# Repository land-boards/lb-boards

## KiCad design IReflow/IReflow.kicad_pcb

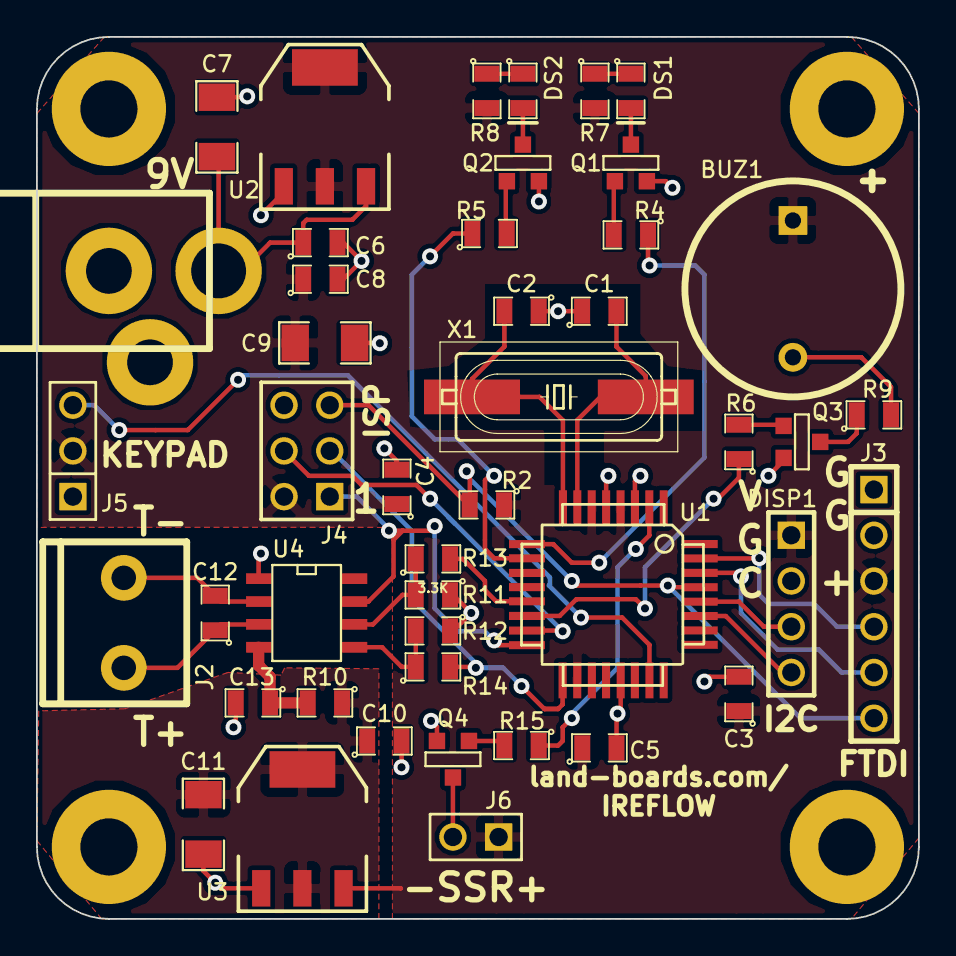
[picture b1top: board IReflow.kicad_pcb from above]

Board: 2 copper layers, 49.0 x 49.0 mm, 49 parts (0 on the bottom side), 36 nets.

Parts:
BUZ1: BUZZER; PIEZO_12MM
C1, C2: 18pF; SM0805
C3, C4, C5, C6, C8, C10, C13: 0.1uF; SM0805
C7, C9, C11: 10uF; SM1206
C12: 0.01uF; SM0805
DISP1: I2C_OLED_128X64; PIN_ARRAY_4X1
DS1, DS2: LED; SM0805
J1: DCJ0202; JACK_2.1MM
J2: CONN_2; TB2-5MM
J3: FTDI; PIN_ARRAY_6X1
J4: ISP; PIN_ARRAY_3X2
J5: GVS; PIN_ARRAY_3X1
J6: CONN_2; PIN_ARRAY_2X1
MTG1, MTG2, MTG3, MTG4: CONN_1; MTG-4-40
Q1, Q2, Q3, Q4: 2N3904; SOT23EBC
R2, R4, R5, R6, R15: 10K; SM0805
R7, R8: 330; SM0805
R9: 100; SM0805
R10: 10; SM0805
R11, R12: 3.3K; SM0805
R13, R14: 2.7K; SM0805
U1: ATMEGA328-AU; TQFP32
U2: AP1117-5.0; SOT223
U3: AP1117; SOT223
U4: MAX31855; SO8E
X1: 16.0MHz; crystal-HC49UP

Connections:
+5V: BUZ1.1, C3.1, C4.1, C5.1, C8.1, C9.1, DISP1.1, J3.3, J4.2, J5.2, J6.1, R2.1, R7.2, R8.2, U1.4, U1.6, U1.18, U2.2, U2.4, U3.3
/CPU/BUZZ: R6.1, U1.14
/CPU/CS: R13.2, U1.13
/CPU/DS1: R4.1, U1.9
/CPU/DS2: R5.1, U1.10
/CPU/MISO: J4.1, U1.16, U4.7
/CPU/MOSI: J4.4, U1.15
/CPU/RESET: J3.6, J4.5, R2.2, U1.29
/CPU/RXD: J3.5, U1.30
/CPU/SCK: J4.3, R14.2, U1.17
/CPU/SCL: DISP1.3, U1.28
/CPU/SDA: DISP1.4, U1.27
/CPU/SSR: R15.1, U1.2
/CPU/SW5WAY: J5.3, U1.23
/CPU/TXD: J3.4, U1.31
/CPU/XTAL1: C1.2, U1.7, X1.2
/CPU/XTAL2: C2.2, U1.8, X1.1
/Power Supply/+3.3V: C10.1, C11.1, R10.1, U3.2, U3.4
/Thermocoupler Amplifier/THERMO+: C12.1, J2.1, U4.3
/Thermocoupler Amplifier/THERMO-: C12.2, J2.2, U4.2
/Thermocoupler Amplifier/V33COND: C13.1, R10.2, U4.4
GND: C1.1, C2.1, C3.2, C4.2, C5.2, C6.2, C7.2, C8.2, C9.2, C10.2, C11.2, C13.2, DISP1.2, J1.2, J1.3, J3.1, J3.2, J4.6, J5.1, Q1.1, Q2.1, Q3.1, Q4.1, R11.1, R12.1, U1.3, U1.5, U1.21, U2.1, U3.1, U4.1
unnamed: Q3.3, R9.1
unnamed: J6.2, Q4.3
unnamed: Q4.2, R15.2
unnamed: Q1.2, R4.2
unnamed: DS1.1, R7.1
unnamed: DS1.2, Q1.3
unnamed: Q3.2, R6.2
unnamed: BUZ1.2, R9.2
unnamed: DS2.1, R8.1
unnamed: DS2.2, Q2.3
unnamed: Q2.2, R5.2
unnamed: R11.2, R13.1, U4.6
unnamed: R12.2, R14.1, U4.5
unnamed: C6.1, C7.1, J1.1, U2.3

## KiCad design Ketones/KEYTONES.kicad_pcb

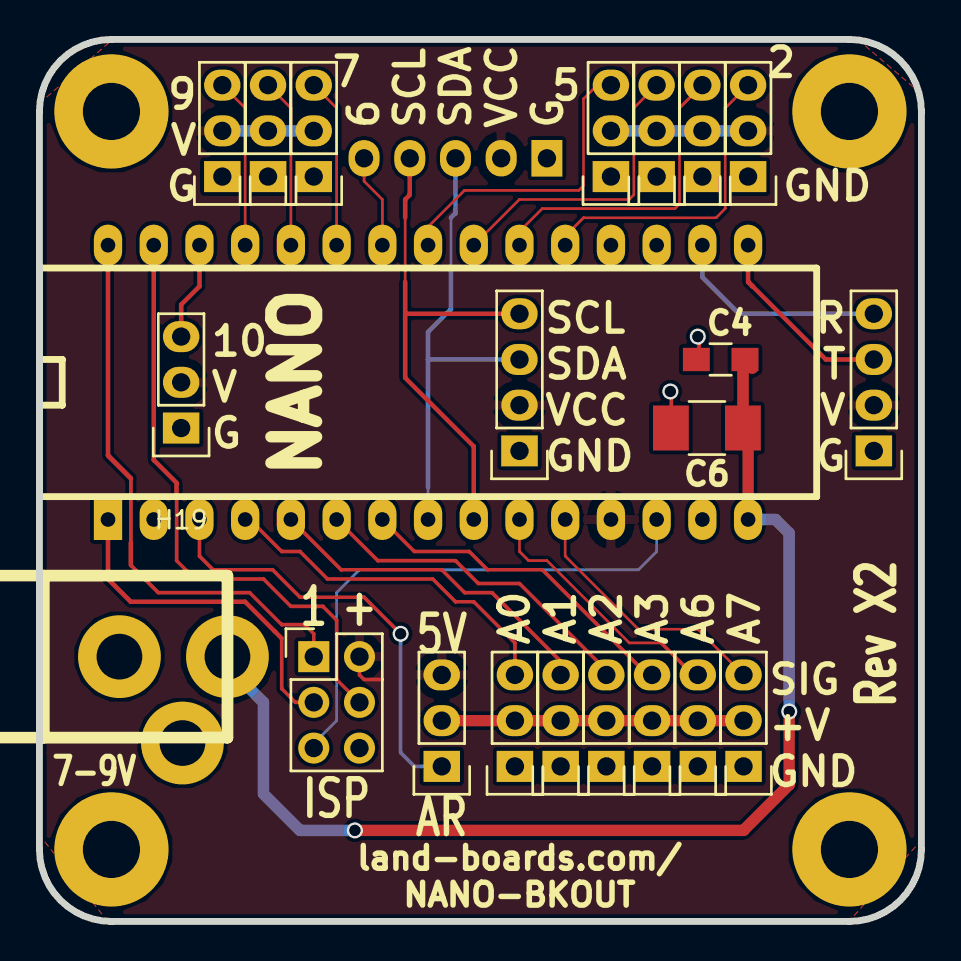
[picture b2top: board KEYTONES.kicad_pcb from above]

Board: 2 copper layers, 49.0 x 49.0 mm, 27 parts (1 on the bottom side), 28 nets.

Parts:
C4: 0.1uF; R_0805_HandSoldering
C6: 22uF; R_1210_HandSoldering
H1, H2, H3, H4, H5, H6, H9, H10, H11, H12, H14, H15, H16, H18, H19: CONN_01X03; Pin_Header_Straight_1x03
H7: CONN_01X05; Pin_Header_Straight_1x05
H8: CONN_02X03; Pin_Header_Straight_2x03
H13, H17: CONN_01X04; Pin_Header_Straight_1x04
J1: DCJ0202; DCJ-NEW
MTG1, MTG2, MTG3, MTG4: CONN_1; MTG-4-40
U5: arduino_nano; arduino_mini

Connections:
+5V: H7.2, H8.2, H9.2, H10.2, H11.2, H12.2, H13.2, H14.2, H15.2, H16.2, H17.2, H18.3, H19.2, U5.12
+9V: C4.1, C6.1, J1.1, U5.15
/A0: H1.3, U5.4
/A1: H2.3, U5.5
/A2: H3.3, U5.6
/A3: H4.3, U5.7
/A6: H5.3, U5.10
/A7: H6.3, U5.11
/AREF: H18.1, U5.3
/D0: H17.3, U5.16
/D1: H17.4, U5.17
/D2: H16.3, U5.20
/D3: H15.3, U5.21
/D4: H14.3, U5.22
/D5: H12.3, U5.23
/D6: H7.5, U5.24
/D7: H11.3, U5.25
/D8: H10.3, U5.26
/D9: H9.3, U5.27
/D10: H19.3, U5.28
/D11: H8.4, U5.29
/D12: H8.1, U5.30
/D13: H8.3, U5.1
/SCL: H7.4, H13.4, U5.9
/SDA: H7.3, H13.3, U5.8
/~RST: H8.5, U5.13
GND: C4.2, C6.2, H1.1, H2.1, H3.1, H4.1, H5.1, H6.1, H7.1, H8.6, H9.1, H10.1, H11.1, H12.1, H13.1, H14.1, H15.1, H16.1, H17.1, H19.1, J1.2, J1.3, U5.14, U5.19
unnamed: H1.2, H2.2, H3.2, H4.2, H5.2, H6.2, H18.2

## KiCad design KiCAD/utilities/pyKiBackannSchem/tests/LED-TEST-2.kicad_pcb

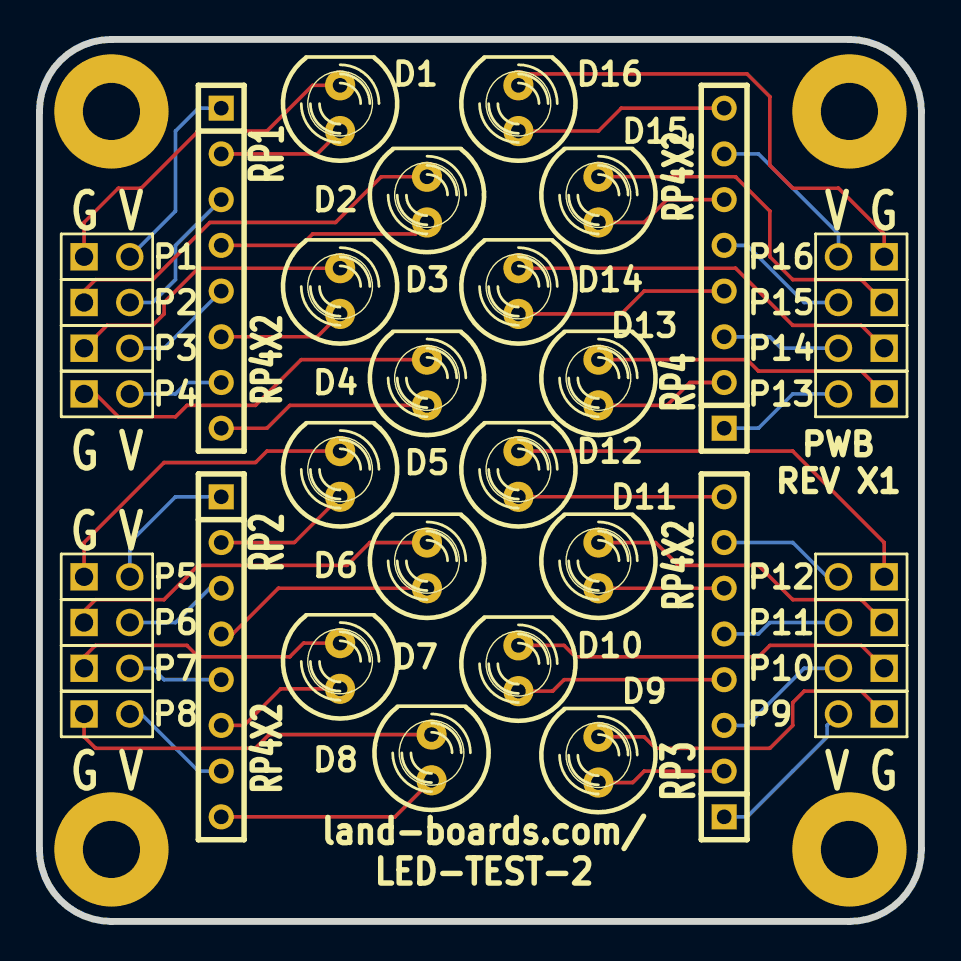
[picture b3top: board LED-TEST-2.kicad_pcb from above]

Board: 2 copper layers, 49.0 x 49.0 mm, 40 parts (0 on the bottom side), 48 nets.

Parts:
D1, D2, D3, D4, D5, D6, D7, D8, D9, D10, D11, D12, D13, D14, D15, D16: LED; LED-5MM
MTG1, MTG2, MTG3, MTG4: CONN_1; MTG-4-40
P1, P2, P3, P4, P5, P6, P7, P8, P9, P10, P11, P12, P13, P14, P15, P16: CONN_2; PIN_ARRAY_2X1
RP1, RP2, RP3, RP4: RP4X2; SIL-8

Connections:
unnamed: D1.1, RP1.2
unnamed: D1.2, P1.1
unnamed: D2.1, RP1.4
unnamed: D2.2, P2.1
unnamed: D3.1, RP1.6
unnamed: D3.2, P3.1
unnamed: D4.1, RP1.8
unnamed: D4.2, P4.1
unnamed: D5.1, RP2.2
unnamed: D5.2, P5.1
unnamed: D6.1, RP2.4
unnamed: D6.2, P6.1
unnamed: D7.1, RP2.6
unnamed: D7.2, P7.1
unnamed: D8.1, RP2.8
unnamed: D8.2, P8.1
unnamed: D9.1, RP3.2
unnamed: D9.2, P9.1
unnamed: D10.1, RP3.4
unnamed: D10.2, P10.1
unnamed: D11.1, RP3.6
unnamed: D11.2, P11.1
unnamed: D12.1, RP3.8
unnamed: D12.2, P12.1
unnamed: D13.1, RP4.2
unnamed: D13.2, P13.1
unnamed: D14.1, RP4.4
unnamed: D14.2, P14.1
unnamed: D15.1, RP4.6
unnamed: D15.2, P15.1
unnamed: D16.1, RP4.8
unnamed: D16.2, P16.1
unnamed: P1.2, RP1.1
unnamed: P2.2, RP1.3
unnamed: P3.2, RP1.5
unnamed: P4.2, RP1.7
unnamed: P5.2, RP2.1
unnamed: P6.2, RP2.3
unnamed: P7.2, RP2.5
unnamed: P8.2, RP2.7
unnamed: P9.2, RP3.1
unnamed: P10.2, RP3.3
unnamed: P11.2, RP3.5
unnamed: P12.2, RP3.7
unnamed: P13.2, RP4.1
unnamed: P14.2, RP4.3
unnamed: P15.2, RP4.5
unnamed: P16.2, RP4.7

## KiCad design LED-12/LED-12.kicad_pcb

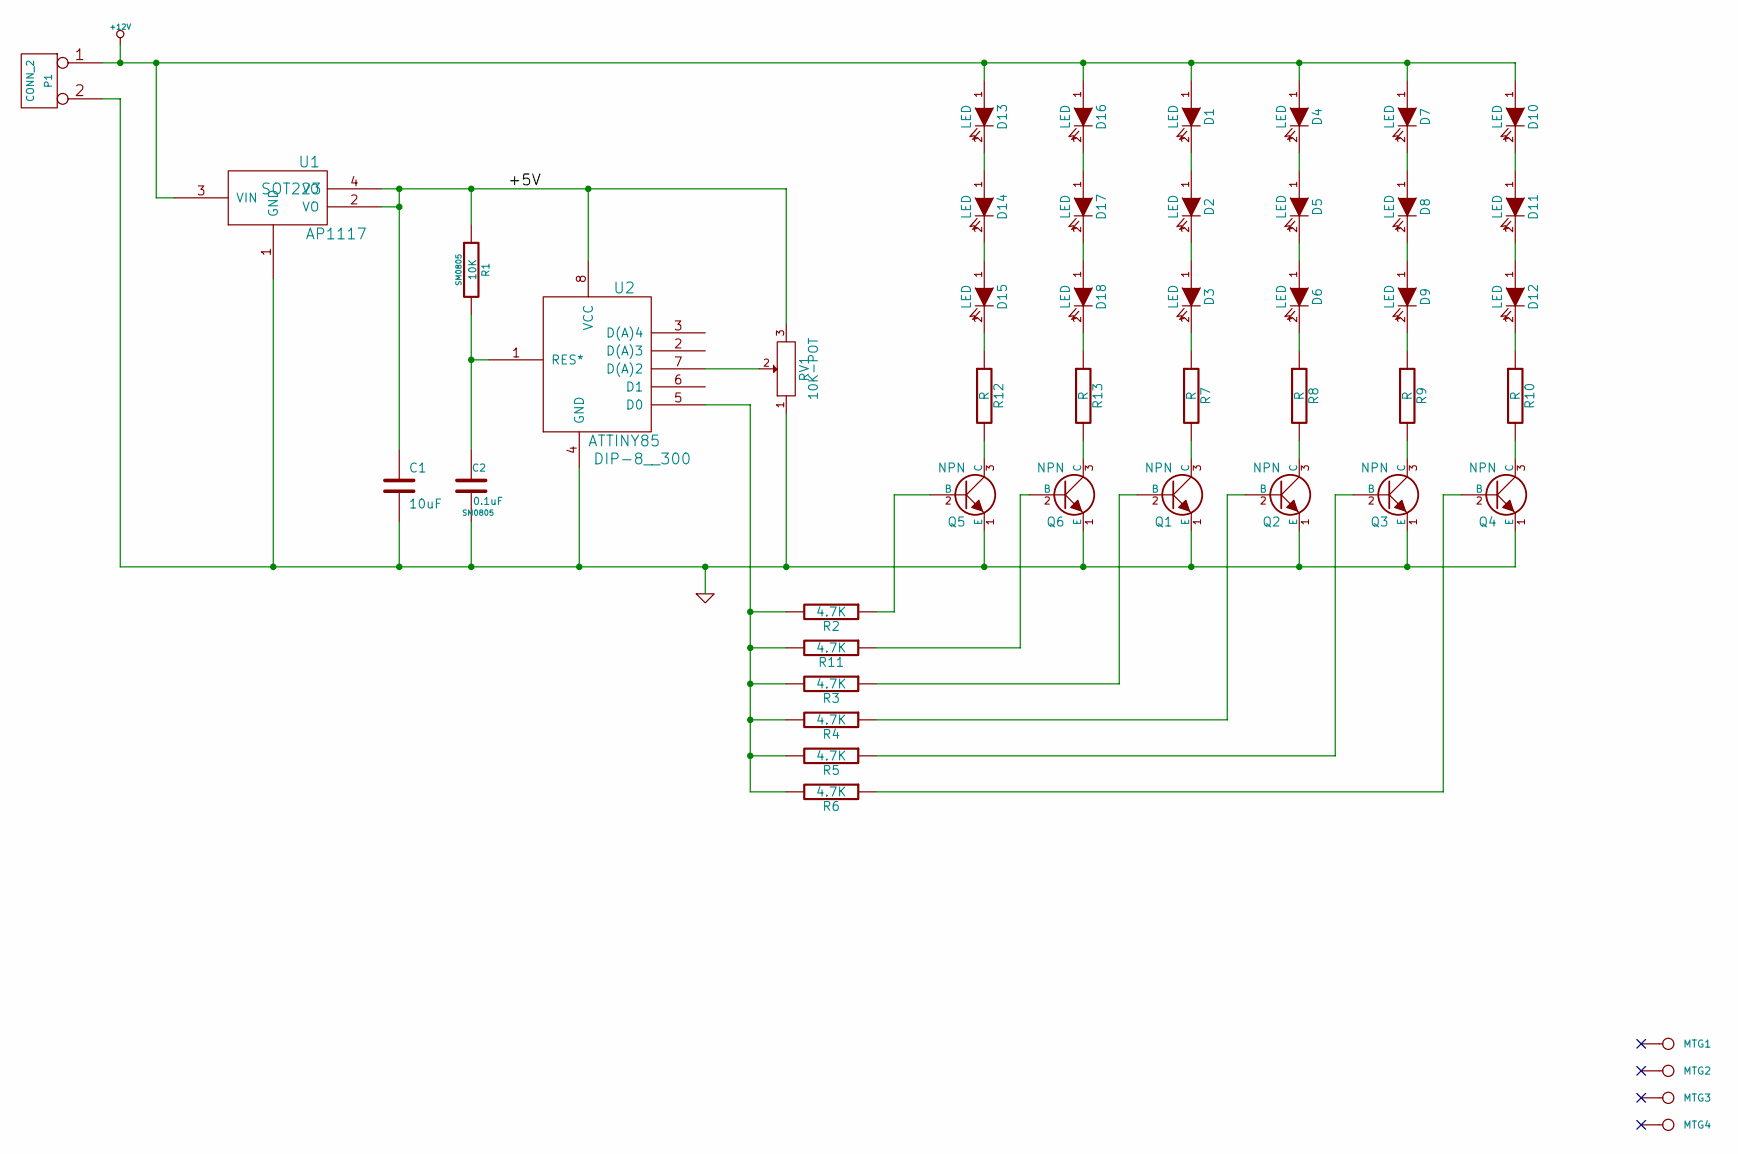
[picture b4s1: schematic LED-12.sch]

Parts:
C1: 10uF; SM1210
C2: 0.1uF; SM0805
D1, D2, D3, D4, D5, D6, D7, D8, D9, D10, D11, D12, D13, D14, D15, D16, D17, D18: LED; LED-5MM
MTG1, MTG2, MTG3, MTG4: CONN_1; MTG-4-40
P1: CONN_2; TB2-5MM
Q1, Q2, Q3, Q4, Q5, Q6: NPN; TO92-123
R1: 10K; SM0805
R2, R3, R4, R5, R6, R11: 4.7K; SM0805
R7, R8, R9, R10, R12, R13: R; SM0805
RV1: 10K-POT; PIN_ARRAY_3X1
U1: AP1117; SOT223
U2: ATTINY85; DIP-8__300

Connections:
+12V: D1.1 (A), D4.1 (A), D7.1 (A), D10.1 (A), D13.1 (A), D16.1 (A), P1.1, U1.3 (VIN)
/+5V: C1.1, R1.1, RV1.3, U1.2 (VO), U1.4 (VO), U2.8 (VCC)
GND: C1.2, C2.2, P1.2 (PM), Q1.1 (E), Q2.1 (E), Q3.1 (E), Q4.1 (E), Q5.1 (E), Q6.1 (E), RV1.1, U1.1 (GND), U2.4 (GND)
unnamed: C2.1, R1.2, U2.1 (RES*)
unnamed: RV1.2, U2.7 (D(A)2)
unnamed: D16.2 (K), D17.1 (A)
unnamed: D17.2 (K), D18.1 (A)
unnamed: D18.2 (K), R13.1
unnamed: Q5.2 (B), R2.1
unnamed: Q5.3 (C), R12.2
unnamed: Q6.2 (B), R11.1
unnamed: D15.2 (K), R12.1
unnamed: Q1.2 (B), R3.1
unnamed: Q2.2 (B), R4.1
unnamed: Q3.2 (B), R5.1
unnamed: Q4.2 (B), R6.1
unnamed: Q6.3 (C), R13.2
unnamed: D13.2 (K), D14.1 (A)
unnamed: D14.2 (K), D15.1 (A)
unnamed: Q1.3 (C), R7.2
unnamed: D3.2 (K), R7.1
unnamed: Q3.3 (C), R9.2
unnamed: D9.2 (K), R9.1
unnamed: D8.2 (K), D9.1 (A)
unnamed: D7.2 (K), D8.1 (A)
unnamed: D10.2 (K), D11.1 (A)
unnamed: D11.2 (K), D12.1 (A)
unnamed: D12.2 (K), R10.1
unnamed: Q4.3 (C), R10.2
unnamed: Q2.3 (C), R8.2
unnamed: D6.2 (K), R8.1
unnamed: D5.2 (K), D6.1 (A)
unnamed: D4.2 (K), D5.1 (A)
unnamed: D1.2 (K), D2.1 (A)
unnamed: D2.2 (K), D3.1 (A)
unnamed: R2.2, R3.2, R4.2, R5.2, R6.2, R11.2, U2.5 (D0)

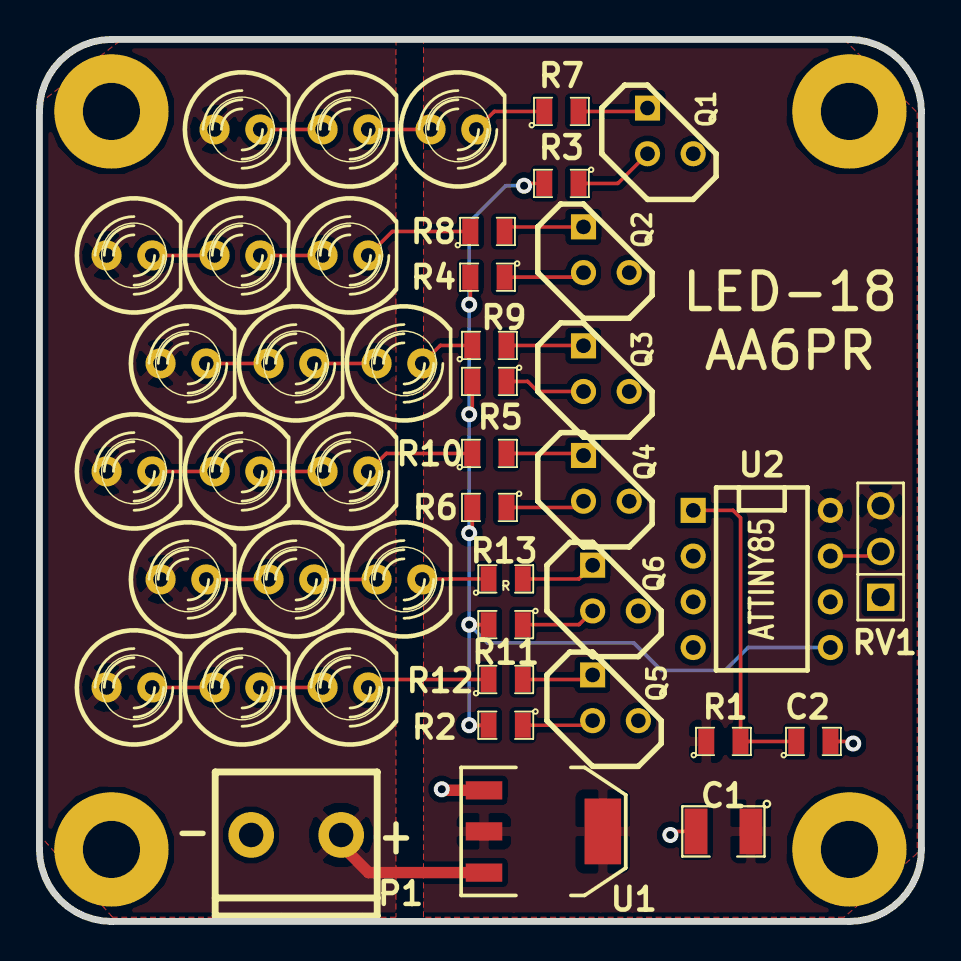
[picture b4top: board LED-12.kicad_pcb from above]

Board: 2 copper layers, 49.0 x 49.0 mm, 47 parts (0 on the bottom side), 36 nets.
